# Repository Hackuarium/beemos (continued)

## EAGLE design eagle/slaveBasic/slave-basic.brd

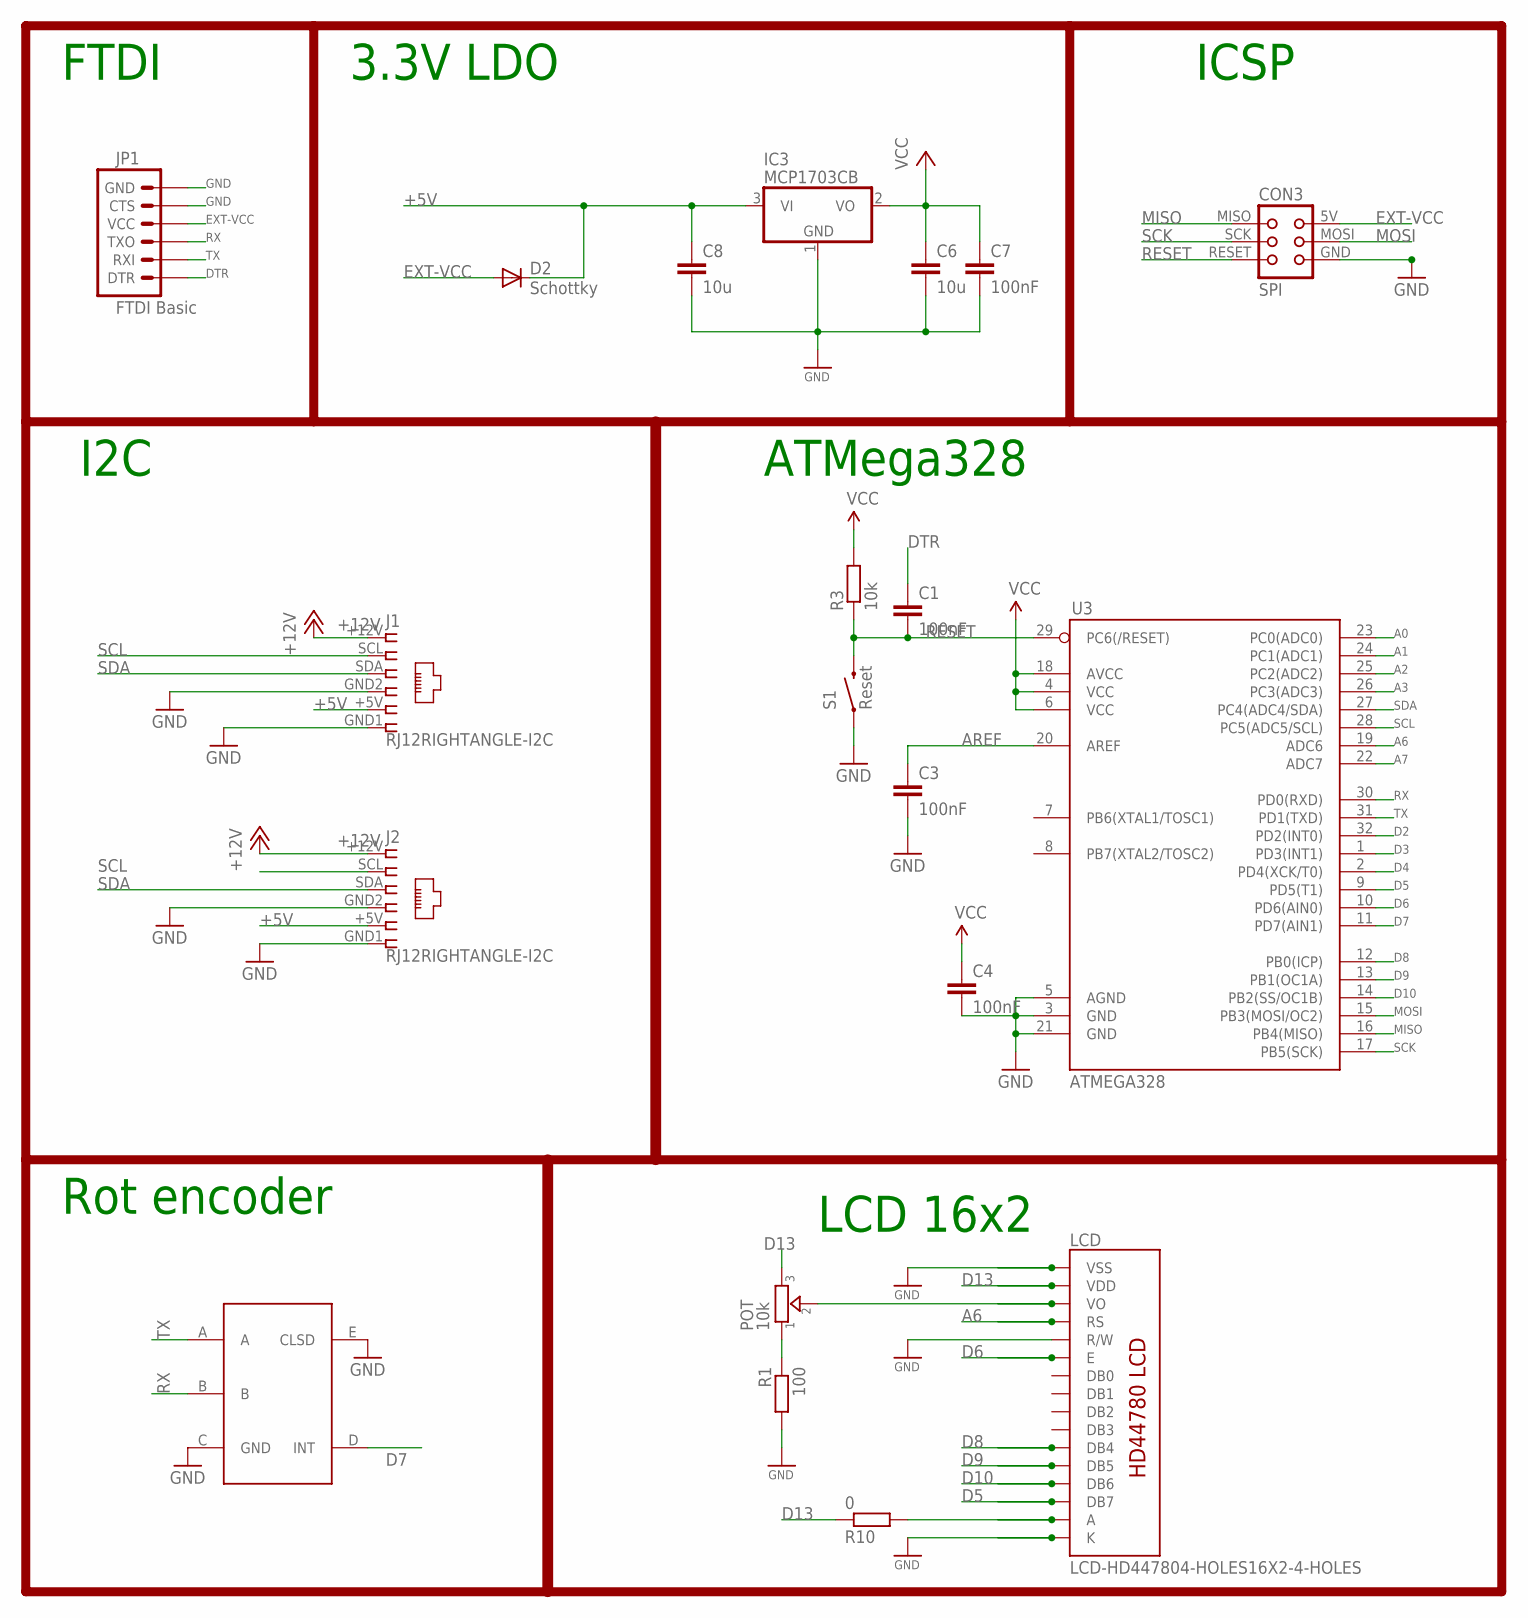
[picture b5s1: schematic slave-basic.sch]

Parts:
C1, C3, C4, C7: 100nF; C0805K; MPN 80-C1206C104K5R; LCSC C49678
C6, C8: 10u; C0805K; MPN 77-VJ1206V106ZXQTBC; LCSC C15850
CON3: SPI; TC2030-MCP
D2: Schottky; SOD123; MPN 621-1N5819HW-F; LCSC C82544
IC3: MCP1703CB; SOT23; LCSC C53352
J1, J2: RJ12RIGHTANGLE-I2C; RJ12-RIGHTANGLE-I2C
JP1: FTDI Basic; 1X06
LCD: LCD-HD447804-HOLES16X2-4-HOLES; LCD-16X2-4HOLES
POT: 10k; TRIMMER_3362P
R1: 100; R0805; LCSC C17408
R3: 10k; R0805; LCSC C17513
R10: 0; R0805; LCSC C17477
S1: Reset; TACTILE-SWITCH-SMD-ALT01
U3: ATMEGA328; TQFP32-08
U$1: EC11E

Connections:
+5V: C8.1, D2.C, IC3.3 (VI), J1.+5V (5), J2.+5V (5)
+12V: J1.+12V (1), J2.+12V (1)
A0: U3.23 (PC0(ADC0))
A1: U3.24 (PC1(ADC1))
A2: U3.25 (PC2(ADC2))
A3: U3.26 (PC3(ADC3))
A6: LCD.4 (RS), U3.19 (ADC6)
A7: U3.22 (ADC7)
AREF: C3.1, U3.20 (AREF)
D2: U3.32 (PD2(INT0))
D3: U3.1 (PD3(INT1))
D4: U3.2 (PD4(XCK/T0))
D5: LCD.14 (DB7), U3.9 (PD5(T1))
D6: LCD.6 (E), U3.10 (PD6(AIN0))
D7: U3.11 (PD7(AIN1)), U$1.D (INT)
D8: LCD.11 (DB4), U3.12 (PB0(ICP))
D9: LCD.12 (DB5), U3.13 (PB1(OC1A))
D10: LCD.13 (DB6), U3.14 (PB2(SS/OC1B))
D13: LCD.2 (VDD), POT.3, R10.1
DTR: C1.1, JP1.1 (DTR)
EXT-VCC: CON3.5V (VCC), D2.A, JP1.4 (VCC)
GND: C3.2, C4.2, C6.2, C7.2, C8.2, CON3.GND, IC3.1 (GND), J1.GND1 (6), J1.GND2 (4), J2.GND1 (6), J2.GND2 (4), JP1.5 (CTS), JP1.6 (GND), LCD.1 (VSS), LCD.5 (R/W), LCD.16 (K), R1.2, S1.1, S1.2 (1), U3.3 (GND), U3.5 (AGND), U3.21 (GND), U$1.C (GND), U$1.E (CLSD)
MISO: CON3.MISO, U3.16 (PB4(MISO))
MOSI: CON3.MOSI, U3.15 (PB3(MOSI/OC2))
unnamed: LCD.3 (VO), POT.2
unnamed: POT.1, R1.1
unnamed: LCD.15 (A), R10.2
RESET: C1.2, CON3.RESET, R3.1, S1.3 (2), S1.4 (2), U3.29 (PC6(/RESET))
RX: JP1.3 (TXO), U3.30 (PD0(RXD)), U$1.B
SCK: CON3.SCK, U3.17 (PB5(SCK))
SCL: J1.SCL (2), J2.SCL (2), U3.28 (PC5(ADC5/SCL))
SDA: J1.SDA (3), J2.SDA (3), U3.27 (PC4(ADC4/SDA))
TX: JP1.2 (RXI), U3.31 (PD1(TXD)), U$1.A
VCC: C4.1, C6.1, C7.1, IC3.2 (VO), R3.2, U3.4 (VCC), U3.6 (VCC), U3.18 (AVCC)

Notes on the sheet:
ICSP
ATMega328
3.3V LDO
I2C
FTDI
LCD 16x2
Rot encoder

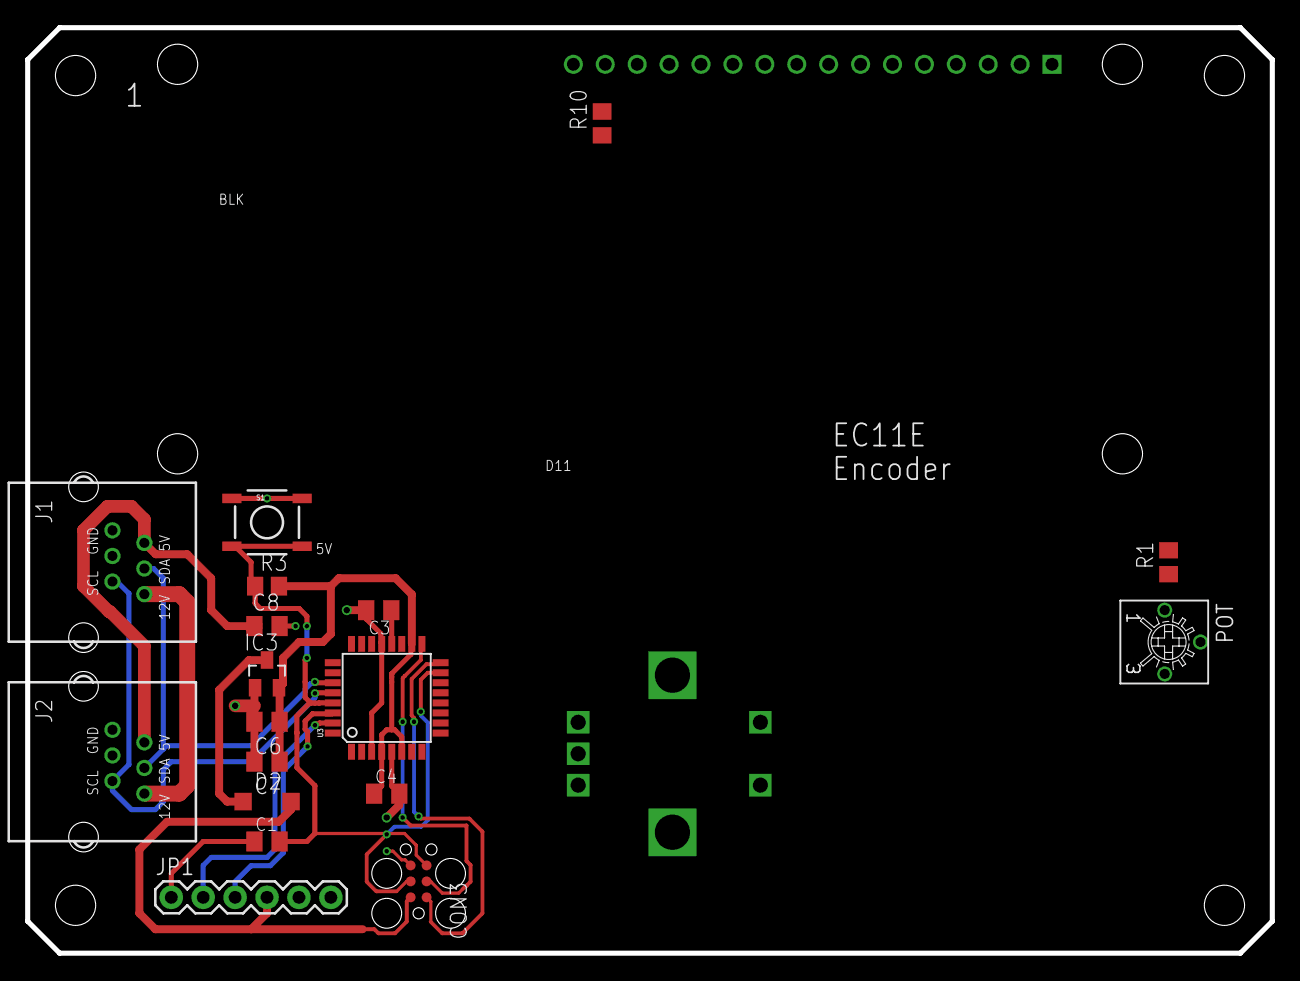
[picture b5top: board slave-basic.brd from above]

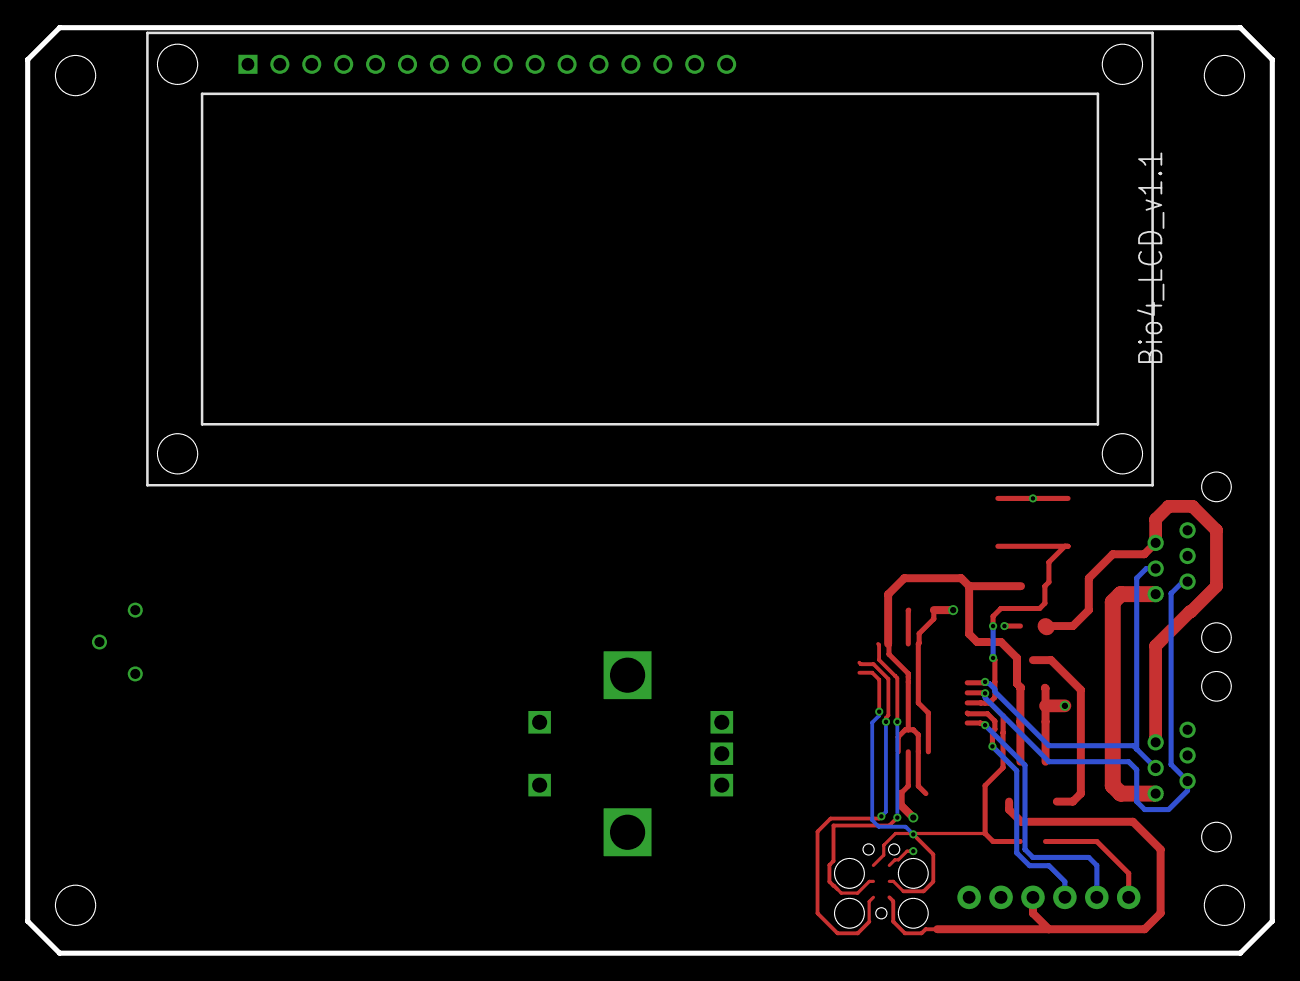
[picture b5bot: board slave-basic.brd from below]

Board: 2 copper layers, 99.1 x 73.7 mm, 20 parts (2 on the bottom side), 26 nets.
